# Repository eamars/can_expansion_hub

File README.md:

1 to 4 CAN Hub
==============
The CAN hub is designed to expand the number of CAN devices without needing to make custom wiring loom. 

BOM
---
* 5x Therminal Block P5.08 4 Rows.

Manufacturing
-------------
BOM (with LCSC part number) and gerber files are provided under [production](production) directory. 

Revisions
* v1.0: Initial release.

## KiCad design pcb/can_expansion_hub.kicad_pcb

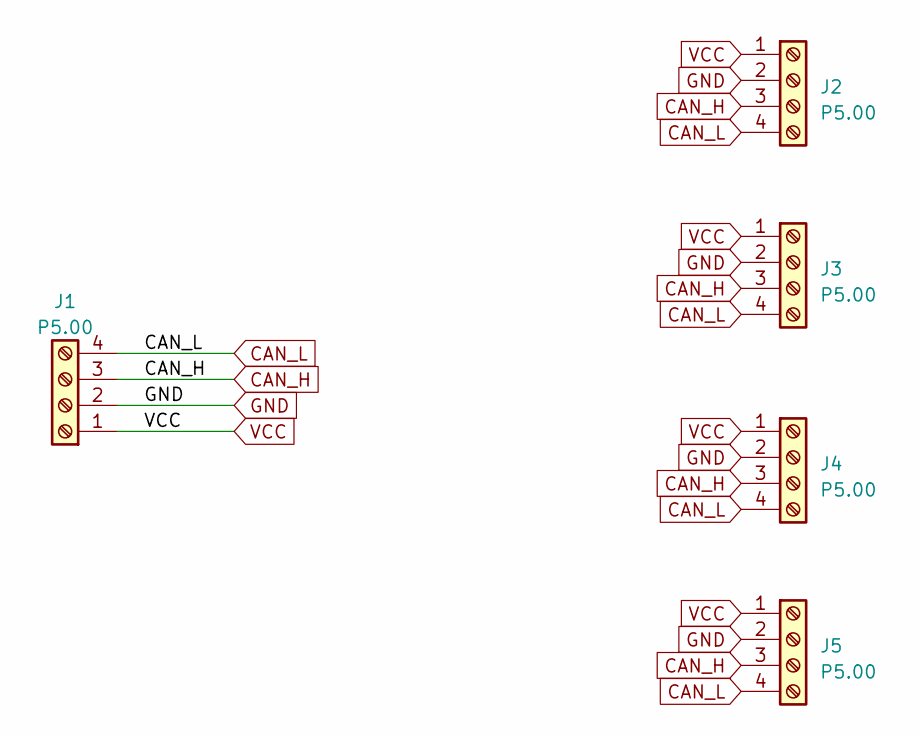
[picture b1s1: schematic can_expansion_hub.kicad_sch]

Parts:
J1, J2, J3, J4, J5: P5.00; TerminalBlock_bornier-4_P5.08mm

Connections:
CAN_H: J1.3, J2.3, J3.3, J4.3, J5.3
CAN_L: J1.4, J2.4, J3.4, J4.4, J5.4
GND: J1.2, J2.2, J3.2, J4.2, J5.2
VCC: J1.1, J2.1, J3.1, J4.1, J5.1

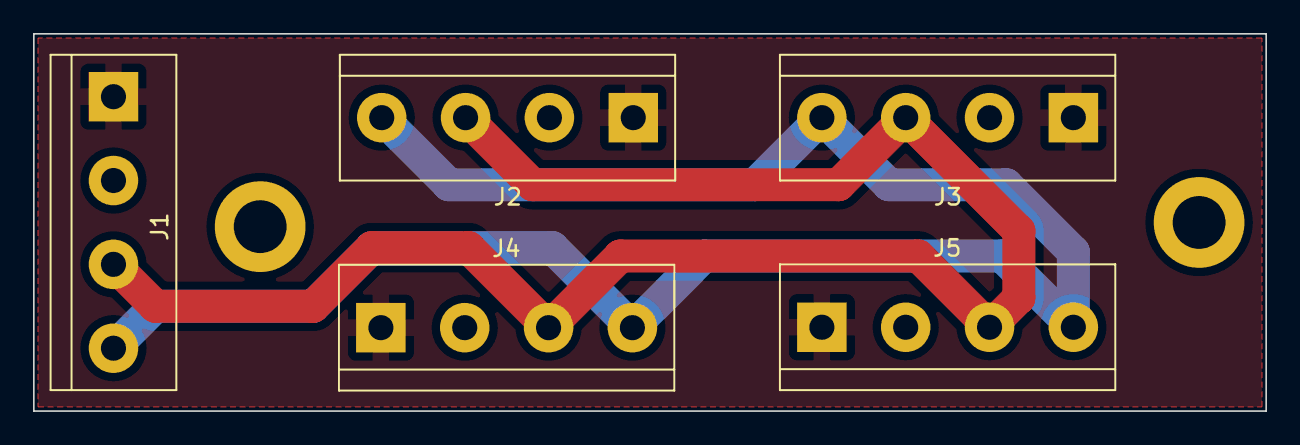
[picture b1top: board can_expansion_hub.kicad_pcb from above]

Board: 2 copper layers, 74.7 x 22.9 mm, 5 parts (0 on the bottom side), 4 nets.

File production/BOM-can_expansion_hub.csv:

Comment,Designator,Footprint,LCSC
P5.00,"J1,J2,J3,J4,J5",TerminalBlock_bornier-4_P5.08mm,C3037697

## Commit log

2023-04-10 Init release
2023-04-10 fix readme
2023-04-10 update image
2023-04-22 Add CAD
2023-06-30 Update 2020 mount, add soldering helper print file
